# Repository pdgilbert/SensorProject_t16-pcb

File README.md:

# SensorProject_t16-pcb
Connect multiple temperature sensors to an analog digital converter.

##  Status: Prototype.

## Summary

Kicad project WIP.

PCB design to connect multiple (up to 16) thermistor temperature sensors to an ads1115 with I2C
output to connect to an MCU. Connectors are  2-pin JST XH_B2B-XH-A, as commonly used on NTC 10K 3950 sensors.
These sensors are inexpensive and easily available in lengths up to 3m. 
Measurements are broadcast with LoRa.

Related software is in repository https://github.com/pdgilbert/SensorProject_t16.

The `.png` and `jpg` files are produced from kicad in the `3D Viewer`  with `File > Export Current View as ...`.

## History

 - Version 0.2.2 2025-09 includes an stm32f411 MCU. It is not yet tested.

 - Version 0.2.0 2025-05 includes an stm32f411 MCU. It has a LoRa module RFM95W.
   It needs some hardware re-adjustment to work.

 - Version 0.1.1 2025-01 has pull up resistors added but has not been manufactured/tested.

 - Version 0.1.0 2024-05 needs manual addition of pull up resistors on the I2C lines. 
   With this modification it works with `blackpill` `stm32f401` or `stm32f411` inserted.
   This versin has no LoRa module.

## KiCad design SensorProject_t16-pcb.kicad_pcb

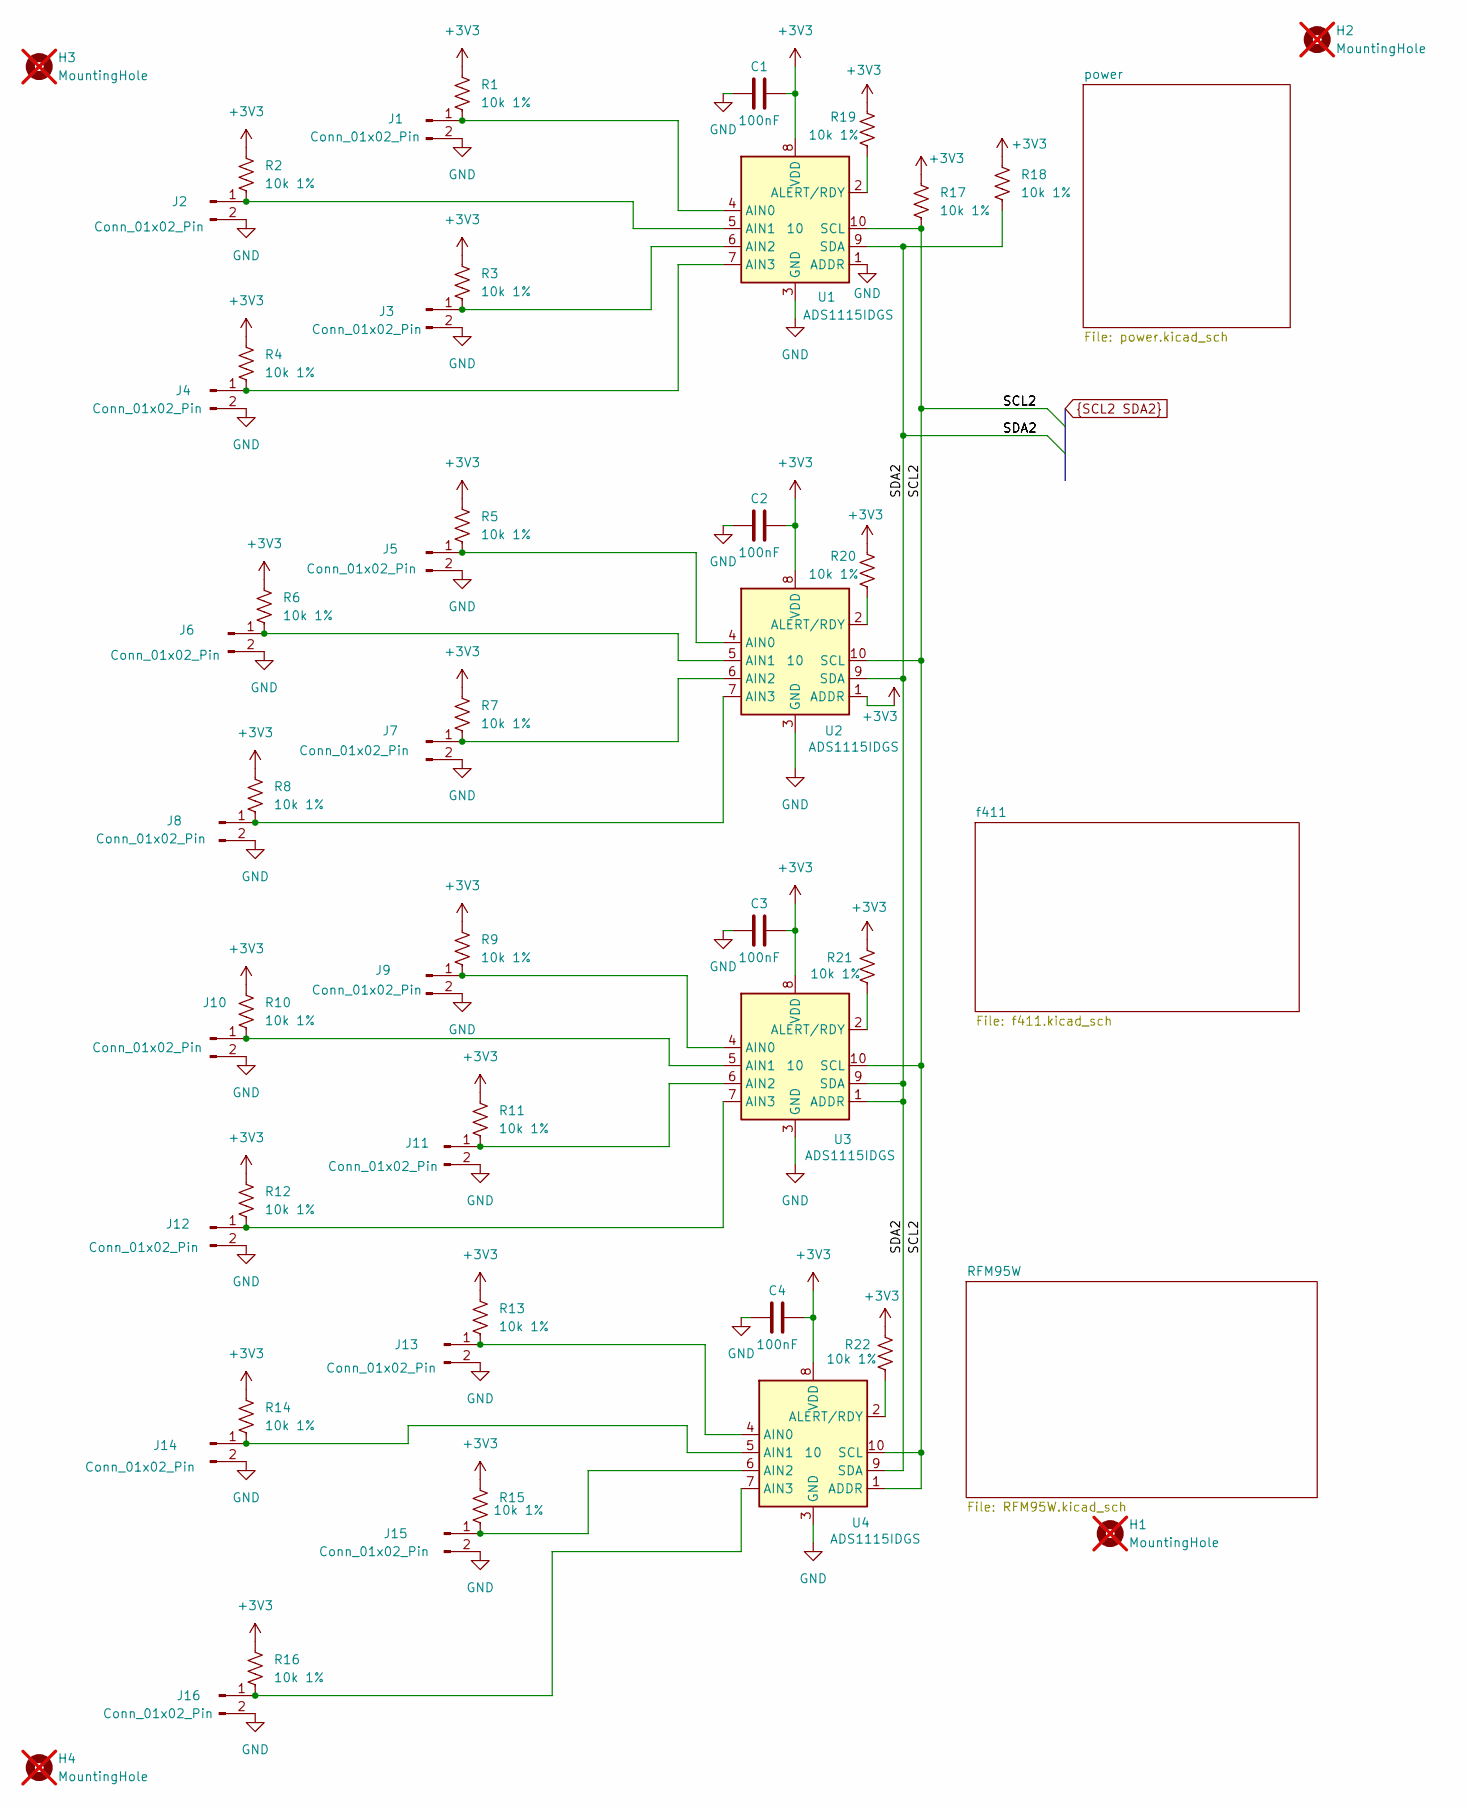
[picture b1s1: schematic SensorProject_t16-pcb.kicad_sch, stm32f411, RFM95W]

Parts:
C1, C2, C3, C4: 100nF; C_0402_1005Metric
H1, H2, H3, H4: MountingHole; MountingHole_2.2mm_M2_ISO7380_Pad; not fitted
J1, J2, J3, J4, J5, J6, J7, J8, J9, J10, J11, J12, J13, J14, J15, J16: Conn_01x02_Pin; JST_XH_B2B-XH-A_1x02_P2.50mm_Vertical; MfgPart B2B-XH-A
R1, R2, R3, R4, R5, R6, R7, R8, R9, R10, R11, R12, R13, R14, R15, R16, R17, R18, R19, R20, R21, R22: 10k 1%; R_0402_1005Metric
U1, U2, U3, U4: ADS1115IDGS; TSSOP-10_3x3mm_P0.5mm; MfgPart ADS1115IDGS

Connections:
+3V3: C1.1, C2.1, C3.1, C4.1, R1.1, R2.1, R3.1, R4.1, R5.1, R6.1, R7.1, R8.1, R9.1, R10.1, R11.1, R12.1, R13.1, R14.1, R15.1, R16.1, R17.1, R18.1, R19.1, R20.1, R21.1, R22.1, U1.8 (VDD), U2.1 (ADDR), U2.8 (VDD), U3.8 (VDD), U4.8 (VDD); also elsewhere on the board
GND: C1.2, C2.2, C3.2, C4.2, J1.2, J2.2, J3.2, J4.2, J5.2, J6.2, J7.2, J8.2, J9.2, J10.2, J11.2, J12.2, J13.2, J14.2, J15.2, J16.2, U1.1 (ADDR), U1.3 (GND), U2.3 (GND), U3.3 (GND), U4.3 (GND); also elsewhere on the board
unnamed: J1.1, R1.2, U1.4 (AIN0)
unnamed: J2.1, R2.2, U1.5 (AIN1)
unnamed: J3.1, R3.2, U1.6 (AIN2)
unnamed: J4.1, R4.2, U1.7 (AIN3)
unnamed: J5.1, R5.2, U2.4 (AIN0)
unnamed: J6.1, R6.2, U2.5 (AIN1)
unnamed: J7.1, R7.2, U2.6 (AIN2)
unnamed: J8.1, R8.2, U2.7 (AIN3)
unnamed: J9.1, R9.2, U3.4 (AIN0)
unnamed: J10.1, R10.2, U3.5 (AIN1)
unnamed: J11.1, R11.2, U3.6 (AIN2)
unnamed: J12.1, R12.2, U3.7 (AIN3)
unnamed: J13.1, R13.2, U4.4 (AIN0)
unnamed: J14.1, R14.2, U4.5 (AIN1)
unnamed: J15.1, R15.2, U4.6 (AIN2)
unnamed: J16.1, R16.2, U4.7 (AIN3)
unnamed: R19.2, U1.2 (ALERT/RDY)
unnamed: R20.2, U2.2 (ALERT/RDY)
unnamed: R21.2, U3.2 (ALERT/RDY)
unnamed: R22.2, U4.2 (ALERT/RDY)
SCL2: R17.2, U1.10 (SCL), U2.10 (SCL), U3.10 (SCL), U4.1 (ADDR), U4.10 (SCL); also elsewhere on the board
SDA2: R18.2, U1.9 (SDA), U2.9 (SDA), U3.1 (ADDR), U3.9 (SDA), U4.9 (SDA); also elsewhere on the board

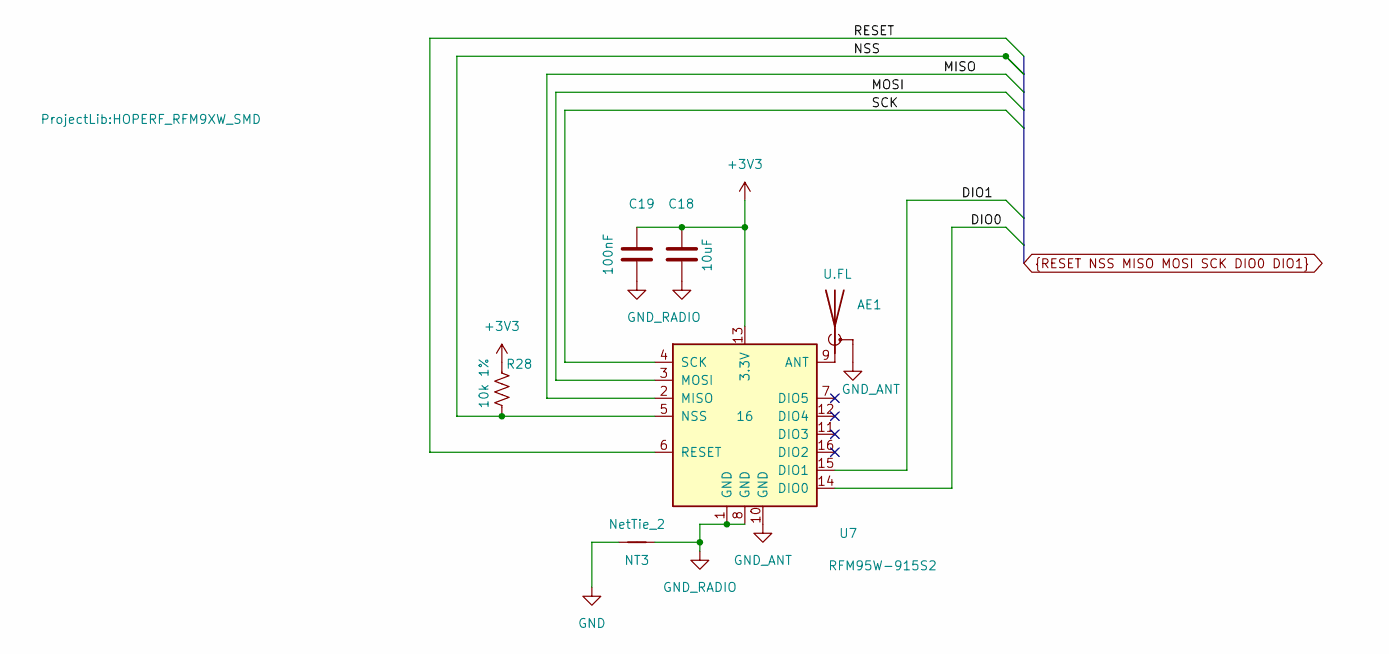
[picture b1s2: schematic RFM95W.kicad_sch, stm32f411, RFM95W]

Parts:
AE1: U.FL; U.FL_Molex_MCRF_73412-0110_Vertical; MfgPart U.FL-R-SMT-K(800)
C18: 10uF; C_0402_1005Metric
C19: 100nF; C_0402_1005Metric
NT3: NetTie_2; NetTie-2_SMD_Pad0.5mm
R28: 10k 1%; R_0402_1005Metric
U7: RFM95W-915S2; HOPERF_RFM9XW_SMD; MfgPart RFM95W-915S2

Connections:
+3V3: C18.1, C19.1, R28.1, U7.13 (3.3V); also elsewhere on the board
DIO0: U7.14 (DIO0); also elsewhere on the board
DIO1: U7.15 (DIO1); also elsewhere on the board
GND: NT3.1; also elsewhere on the board
GND_ANT: AE1.2 (Shield), U7.10 (GND)
GND_RADIO: C18.2, C19.2, NT3.2, U7.1 (GND), U7.8 (GND)
MISO: U7.2 (MISO); also elsewhere on the board
MOSI: U7.3 (MOSI); also elsewhere on the board
NSS: R28.2, U7.5 (NSS); also elsewhere on the board
unnamed: AE1.1 (A), U7.9 (ANT)
RESET: U7.6 (RESET); also elsewhere on the board
SCK: U7.4 (SCK); also elsewhere on the board

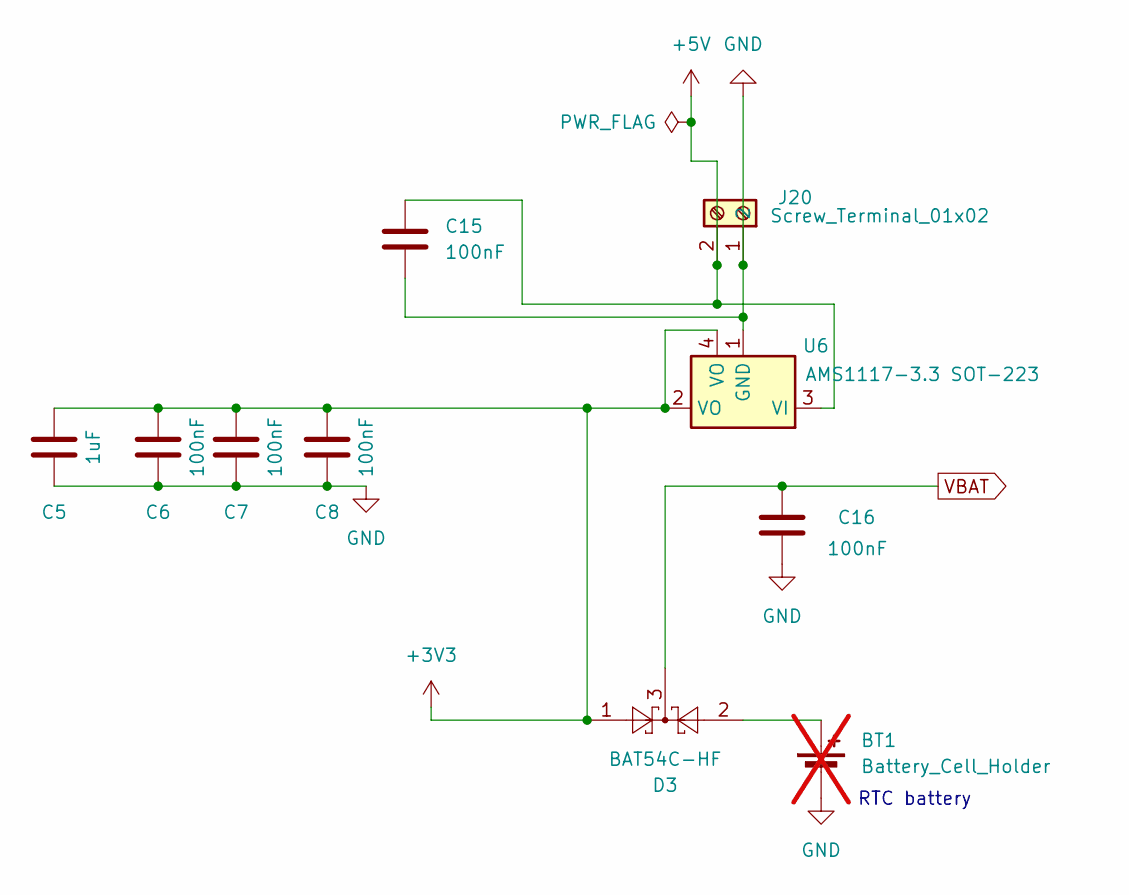
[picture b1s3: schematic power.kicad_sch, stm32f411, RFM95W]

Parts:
BT1: Battery_Cell_Holder; BatteryHolder_LINX_BAT-HLD-012-SMT; MfgPart BAT-HLD-012-SMT; not fitted
C5: 1uF; C_0402_1005Metric
C6, C7, C8, C15, C16: 100nF; C_0402_1005Metric
D3: BAT54C-HF; SOT-23; MfgPart BAT54C-HF
J20: Screw_Terminal_01x02; TerminalBlock_Phoenix_MPT-0,5-2-2.54_1x02_P2.54mm_Horizontal; MfgPart KF128-2.54-2P
U6: AMS1117-3.3 SOT-223; SOT-223; MfgPart AMS1117-3.3

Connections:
+3V3: C5.1, C6.1, C7.1, C8.1, D3.1, U6.2 (VO), U6.4 (VO); also elsewhere on the board
+5V: C15.1, J20.2, U6.3 (VI)
GND: BT1.2 (-), C5.2, C6.2, C7.2, C8.2, C15.2, C16.2, J20.1, U6.1 (GND); also elsewhere on the board
unnamed: BT1.1 (+), D3.2
VBAT: C16.1, D3.3; also elsewhere on the board

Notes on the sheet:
RTC battery

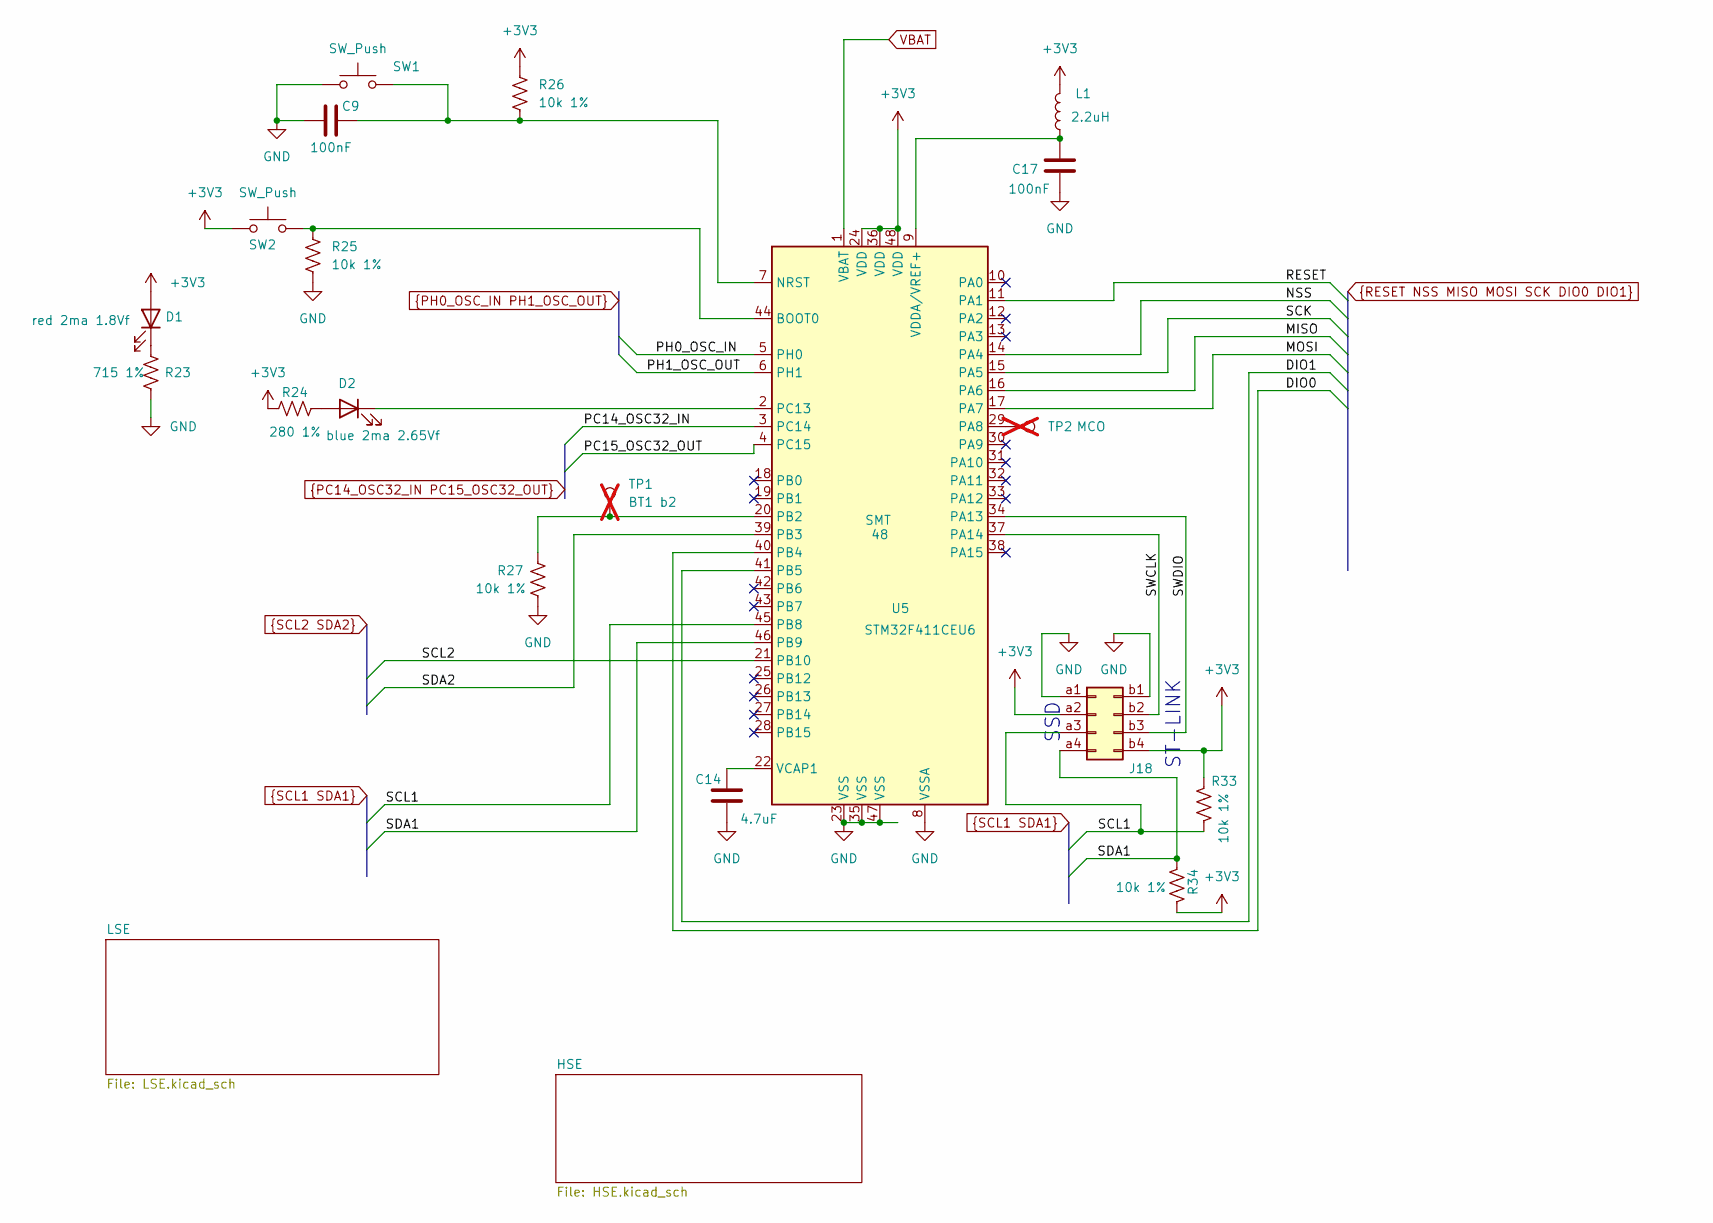
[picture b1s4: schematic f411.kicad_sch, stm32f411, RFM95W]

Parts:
C9, C17: 100nF; C_0402_1005Metric
C14: 4.7uF; C_0402_1005Metric
D1: red 2ma 1.8Vf; LED_0603_1608Metric; MfgPart APT1608LSECK/J3-PRV
D2: blue 2ma 2.65Vf; LED_0603_1608Metric; MfgPart APT1608LVBC/D
J18: Conn_02x04_Top_Bottom; PinSocket_2x04_P2.54mm_Vertical_SMD; MfgPart HC-PM254-5.0H-2x4PS-02A
L1: 2.2uH; L_0402_1005Metric; MfgPart MLZ1005M2R2WT000
R23: 715 1%; R_0402_1005Metric
R24: 280 1%; R_0402_1005Metric
R25, R26, R27, R33, R34: 10k 1%; R_0402_1005Metric
SW1, SW2: SW_Push; SW_SPST_B3U-1000P; MfgPart B3U-1000P
TP1: BT1 b2; TestPoint_Pad_D1.0mm; not fitted
TP2: MCO; TestPoint_Pad_D1.0mm; not fitted
U5: STM32F411CEU6; QFN-48-1EP_7x7mm_P0.5mm_EP5.6x5.6mm; MfgPart STM32F411CEU6

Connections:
+3V3: D1.2 (A), J18.a2, J18.b4, L1.2, R24.1, R26.1, R33.1, R34.2, SW2.1, U5.24 (VDD), U5.36 (VDD), U5.48 (VDD); also elsewhere on the board
/f411/SWCLK: J18.b2, U5.37 (PA14)
/f411/SWDIO: J18.b3, U5.34 (PA13)
DIO0: U5.40 (PB4); also elsewhere on the board
DIO1: U5.41 (PB5); also elsewhere on the board
GND: C9.1, C14.2, C17.2, J18.a1, J18.b1, R23.2, R25.2, R27.2, SW1.1, U5.8 (VSSA), U5.23 (VSS), U5.35 (VSS), U5.47 (VSS), U5.49 (VSS); also elsewhere on the board
MISO: U5.16 (PA6); also elsewhere on the board
MOSI: U5.17 (PA7); also elsewhere on the board
NSS: U5.14 (PA4); also elsewhere on the board
unnamed: D1.1 (K), R23.1
unnamed: D2.2 (A), R24.2
unnamed: D2.1 (K), U5.2 (PC13)
unnamed: R25.1, SW2.2, U5.44 (BOOT0)
unnamed: C9.2, R26.2, SW1.2, U5.7 (NRST)
unnamed: TP2.1 (1_1), U5.29 (PA8)
unnamed: R27.1, TP1.1 (1_1), U5.20 (PB2)
unnamed: C14.1, U5.22 (VCAP1)
unnamed: C17.1, L1.1, U5.9 (VDDA/VREF+)
PC14_OSC32_IN: U5.3 (PC14); also elsewhere on the board
PC15_OSC32_OUT: U5.4 (PC15); also elsewhere on the board
PH0_OSC_IN: U5.5 (PH0); also elsewhere on the board
PH1_OSC_OUT: U5.6 (PH1); also elsewhere on the board
RESET: U5.11 (PA1); also elsewhere on the board
SCK: U5.15 (PA5); also elsewhere on the board
SCL1: J18.a3, R33.2, U5.45 (PB8)
SCL2: U5.21 (PB10); also elsewhere on the board
SDA1: J18.a4, R34.1, U5.46 (PB9)
SDA2: U5.39 (PB3); also elsewhere on the board
VBAT: U5.1 (VBAT); also elsewhere on the board

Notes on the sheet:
SSD
ST-LINK

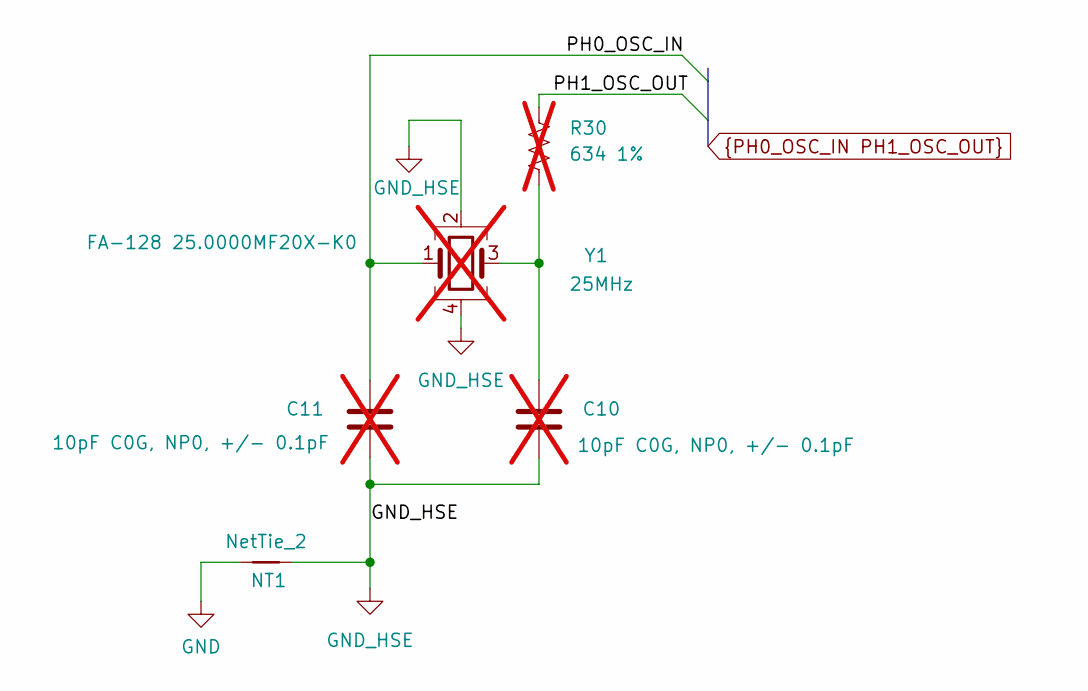
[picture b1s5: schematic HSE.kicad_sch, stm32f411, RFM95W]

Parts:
C10, C11: 10pF C0G, NP0, +/- 0.1pF; C_0402_1005Metric; not fitted
NT1: NetTie_2; NetTie-2_SMD_Pad0.5mm
R30: 634 1%; R_0402_1005Metric; not fitted
Y1: 25MHz; Crystal_SMD_2016-4Pin_2.0x1.6mm; MfgPart FA-128 25.0000MF20X-K0; not fitted

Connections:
GND: NT1.1; also elsewhere on the board
GND_HSE: C10.1, C11.1, NT1.2, Y1.2, Y1.4
unnamed: C10.2, R30.2, Y1.3
PH0_OSC_IN: C11.2, Y1.1; also elsewhere on the board
PH1_OSC_OUT: R30.1; also elsewhere on the board

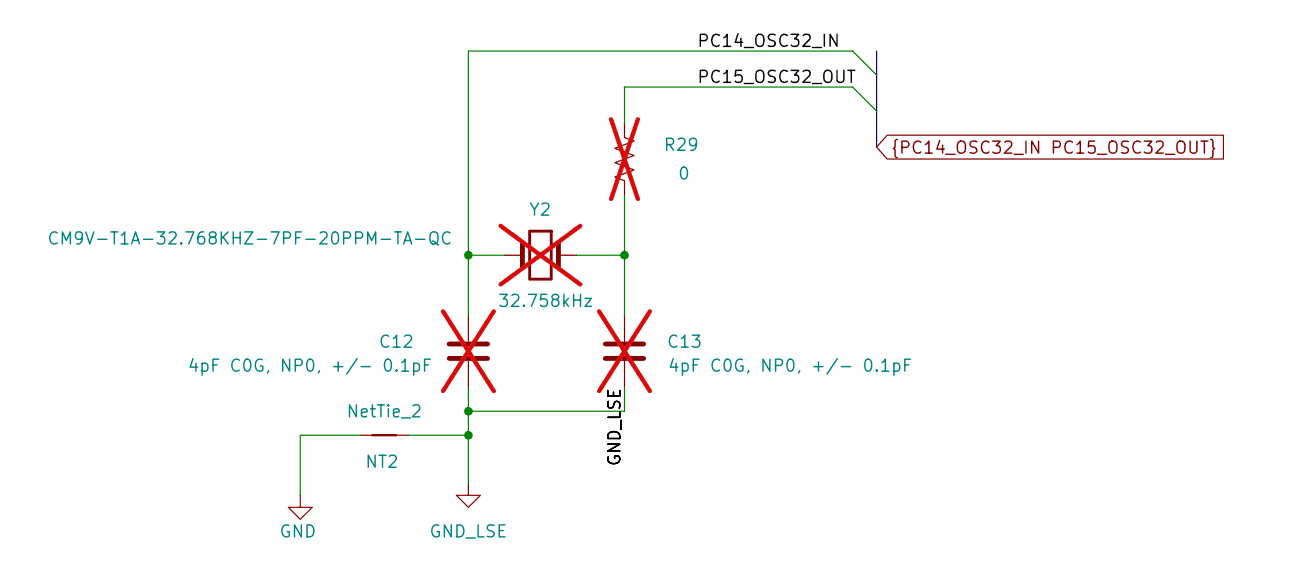
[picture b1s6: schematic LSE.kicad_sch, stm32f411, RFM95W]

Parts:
C12, C13: 4pF C0G, NP0, +/- 0.1pF; C_0402_1005Metric; not fitted
NT2: NetTie_2; NetTie-2_SMD_Pad0.5mm
R29: 0; R_0402_1005Metric; not fitted
Y2: 32.758kHz; Crystal_SMD_MicroCrystal_CM9V-T1A-2Pin_1.6x1.0mm; MfgPart CM9V-T1A-32.768KHZ-7PF-20PPM-TA-QC; not fitted

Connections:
GND: NT2.1; also elsewhere on the board
GND_LSE: C12.1, C13.1, NT2.2
unnamed: C13.2, R29.2, Y2.1
PC14_OSC32_IN: C12.2, Y2.2; also elsewhere on the board
PC15_OSC32_OUT: R29.1; also elsewhere on the board

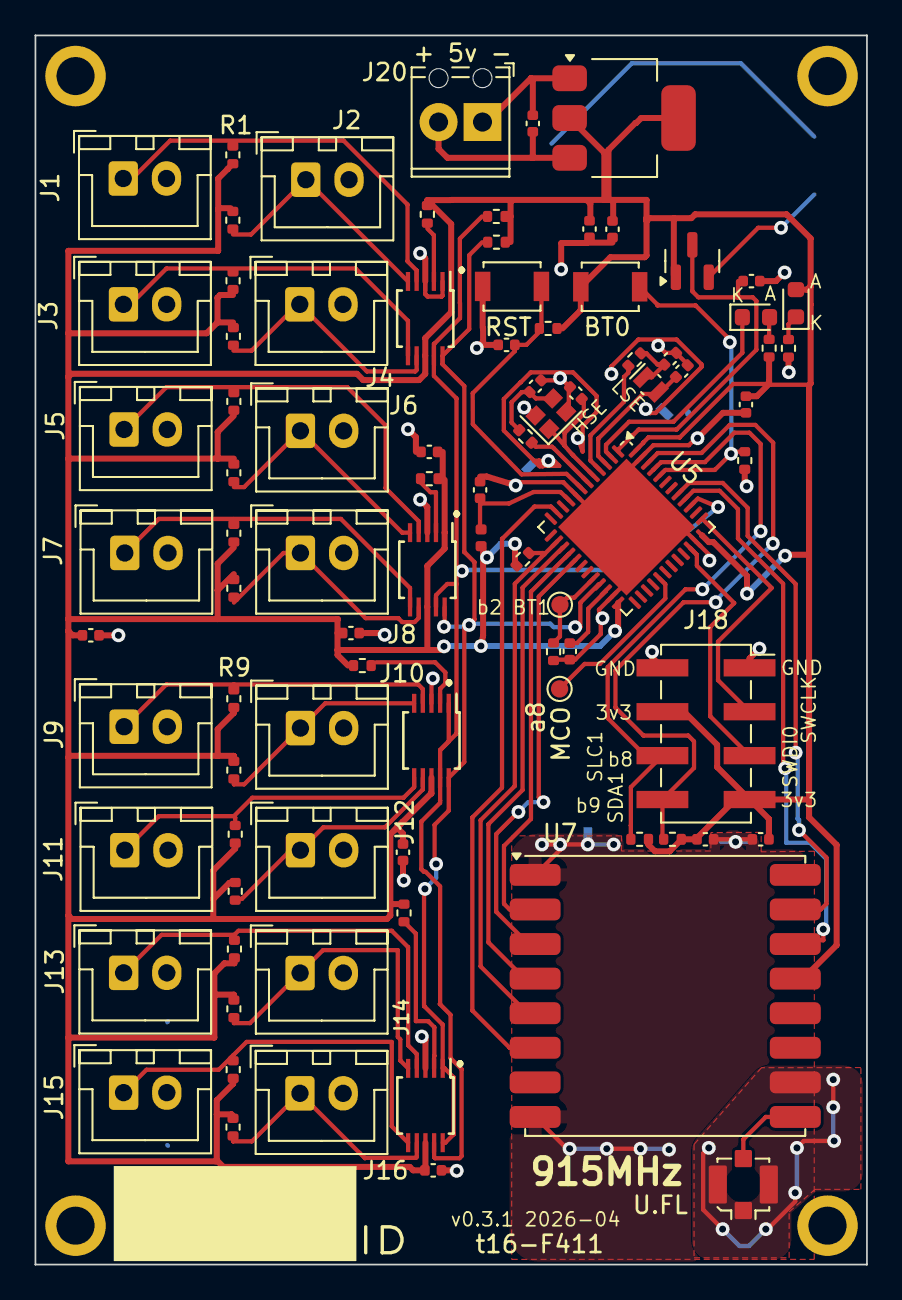
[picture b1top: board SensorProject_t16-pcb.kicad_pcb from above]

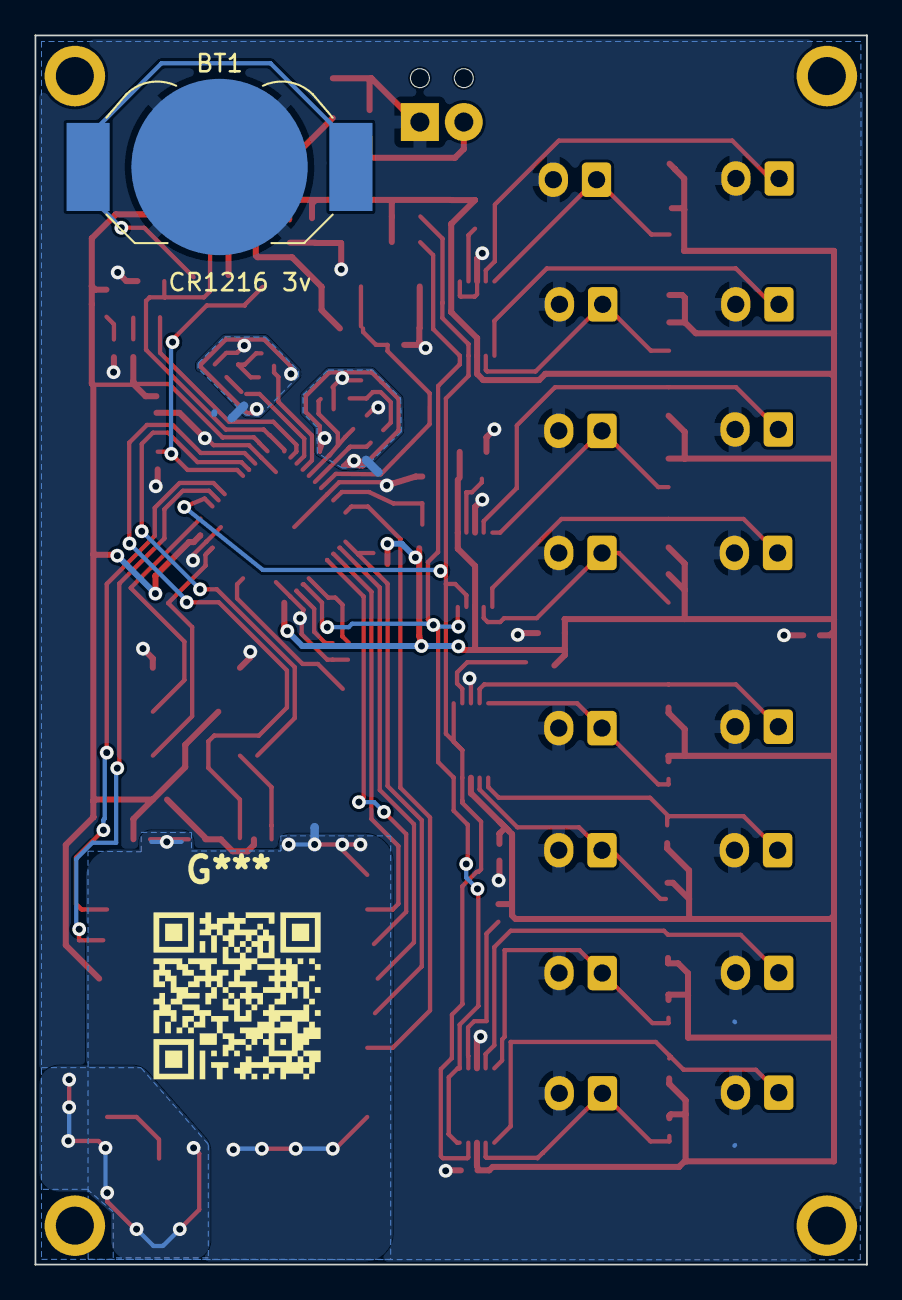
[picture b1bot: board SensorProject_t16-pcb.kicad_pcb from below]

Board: 2 copper layers, 48.1 x 71.1 mm, 95 parts (4 on the bottom side), 58 nets.

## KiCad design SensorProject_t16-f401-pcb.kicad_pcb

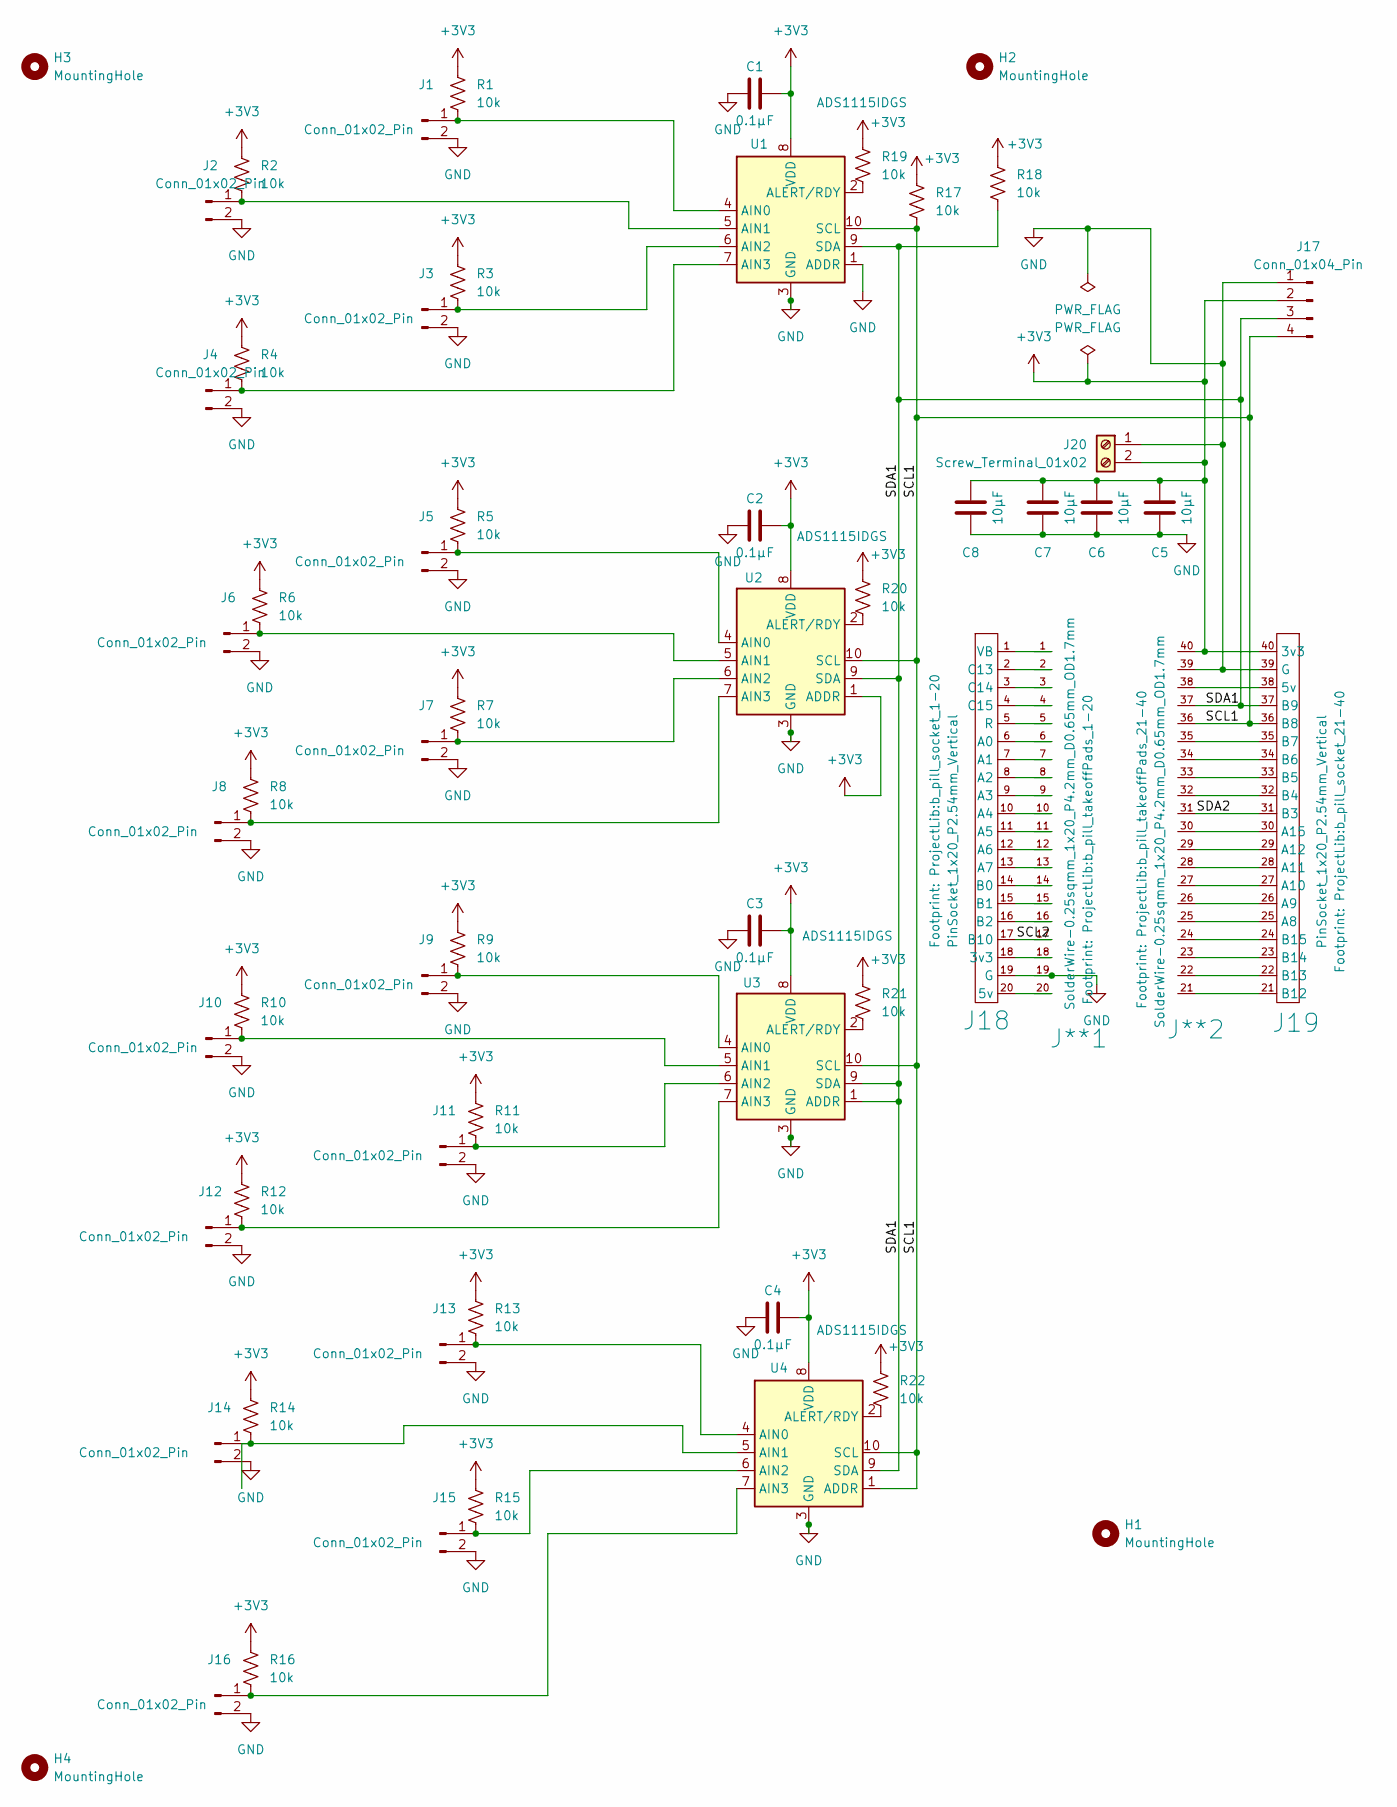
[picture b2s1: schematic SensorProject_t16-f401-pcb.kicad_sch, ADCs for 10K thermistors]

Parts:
C1, C2, C3, C4: 0.1µF; C_0805_2012Metric
C5, C6, C7, C8: 10µF; C_0805_2012Metric
H1, H2, H3, H4: MountingHole; MountingHole_2.2mm_M2_ISO7380_Pad
J1, J2, J3, J4, J5, J6, J7, J8, J9, J10, J11, J12, J13, J14, J15, J16: Conn_01x02_Pin; JST_XH_B2B-XH-A_1x02_P2.50mm_Vertical
J17: Conn_01x04_Pin; JST_XH_B4B-XH-A_1x04_P2.50mm_Vertical
J18: PinSocket_1x20_P2.54mm_Vertical; b_pill_socket_1-20
J19: PinSocket_1x20_P2.54mm_Vertical; b_pill_socket_21-40
J20: Screw_Terminal_01x02; TerminalBlock_Phoenix_MPT-0,5-2-2.54_1x02_P2.54mm_Horizontal
J**1: SolderWire-0.25sqmm_1x20_P4.2mm_D0.65mm_OD1.7mm; b_pill_takeoffPads_1-20
J**2: SolderWire-0.25sqmm_1x20_P4.2mm_D0.65mm_OD1.7mm; b_pill_takeoffPads_21-40
R1, R2, R3, R4, R5, R6, R7, R8, R9, R10, R11, R12, R13, R14, R15, R16, R17, R18, R19, R20, R21, R22: 10k; R_0603_1608Metric
U1, U2, U3, U4: ADS1115IDGS; TSSOP-10_3x3mm_P0.5mm

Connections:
+3V3: C1.1, C2.1, C3.1, C4.1, C5.1, C6.1, C7.1, C8.1, J17.2, J19.40 (3v3), J20.2, J**2.40, R1.1, R2.1, R3.1, R4.1, R5.1, R6.1, R7.1, R8.1, R9.1, R10.1, R11.1, R12.1, R13.1, R14.1, R15.1, R16.1, R17.1, R18.1, R19.1, R20.1, R21.1, R22.1, U1.8 (VDD), U2.1 (ADDR), U2.8 (VDD), U3.8 (VDD), U4.8 (VDD)
/SCL1: J17.4, J19.36 (B8), J**2.36, R17.2, U1.10 (SCL), U2.10 (SCL), U3.10 (SCL), U4.1 (ADDR), U4.10 (SCL)
/SCL2: J18.17 (B10), J**1.17
/SDA1: J17.3, J19.37 (B9), J**2.37, R18.2, U1.9 (SDA), U2.9 (SDA), U3.1 (ADDR), U3.9 (SDA), U4.9 (SDA)
/SDA2: J19.31 (B3), J**2.31
GND: C1.2, C2.2, C3.2, C4.2, C5.2, C6.2, C7.2, C8.2, J1.2, J2.2, J3.2, J4.2, J5.2, J6.2, J7.2, J8.2, J9.2, J10.2, J11.2, J12.2, J13.2, J14.2, J15.2, J16.2, J17.1, J18.19 (G), J19.39 (G), J20.1, J**1.19, J**2.39, U1.1 (ADDR), U1.3 (GND), U2.3 (GND), U3.3 (GND), U4.3 (GND)
unnamed: J1.1, R1.2, U1.4 (AIN0)
unnamed: J2.1, R2.2, U1.5 (AIN1)
unnamed: J3.1, R3.2, U1.6 (AIN2)
unnamed: J4.1, R4.2, U1.7 (AIN3)
unnamed: J5.1, R5.2, U2.4 (AIN0)
unnamed: J6.1, R6.2, U2.5 (AIN1)
unnamed: J7.1, R7.2, U2.6 (AIN2)
unnamed: J8.1, R8.2, U2.7 (AIN3)
unnamed: J9.1, R9.2, U3.4 (AIN0)
unnamed: J10.1, R10.2, U3.5 (AIN1)
unnamed: J11.1, R11.2, U3.6 (AIN2)
unnamed: J12.1, R12.2, U3.7 (AIN3)
unnamed: J13.1, R13.2, U4.4 (AIN0)
unnamed: J14.1, R14.2, U4.5 (AIN1)
unnamed: J15.1, R15.2, U4.6 (AIN2)
unnamed: J16.1, R16.2, U4.7 (AIN3)
unnamed: J18.18 (3v3), J**1.18
unnamed: J18.20 (5v), J**1.20
unnamed: J18.6 (A0), J**1.6
unnamed: J18.7 (A1), J**1.7
unnamed: J18.8 (A2), J**1.8
unnamed: J18.9 (A3), J**1.9
unnamed: J18.10 (A4), J**1.10
unnamed: J18.11 (A5), J**1.11
unnamed: J18.12 (A6), J**1.12
unnamed: J18.13 (A7), J**1.13
unnamed: J18.14 (B0), J**1.14
unnamed: J18.15 (B1), J**1.15
unnamed: J18.16 (B2), J**1.16
unnamed: J18.2 (C13), J**1.2
unnamed: J18.3 (C14), J**1.3
unnamed: J18.4 (C15), J**1.4
unnamed: J18.5 (R), J**1.5
unnamed: J18.1 (VB), J**1.1
unnamed: J19.38 (5v), J**2.38
unnamed: J19.25 (A8), J**2.25
unnamed: J19.26 (A9), J**2.26
unnamed: J19.27 (A10), J**2.27
unnamed: J19.28 (A11), J**2.28
unnamed: J19.29 (A12), J**2.29
unnamed: J19.30 (A15), J**2.30
unnamed: J19.32 (B4), J**2.32
unnamed: J19.33 (B5), J**2.33
unnamed: J19.34 (B6), J**2.34
unnamed: J19.35 (B7), J**2.35
unnamed: J19.21 (B12), J**2.21
unnamed: J19.22 (B13), J**2.22
unnamed: J19.23 (B14), J**2.23
unnamed: J19.24 (B15), J**2.24
unnamed: R19.2, U1.2 (ALERT/RDY)
unnamed: R20.2, U2.2 (ALERT/RDY)
unnamed: R21.2, U3.2 (ALERT/RDY)
unnamed: R22.2, U4.2 (ALERT/RDY)

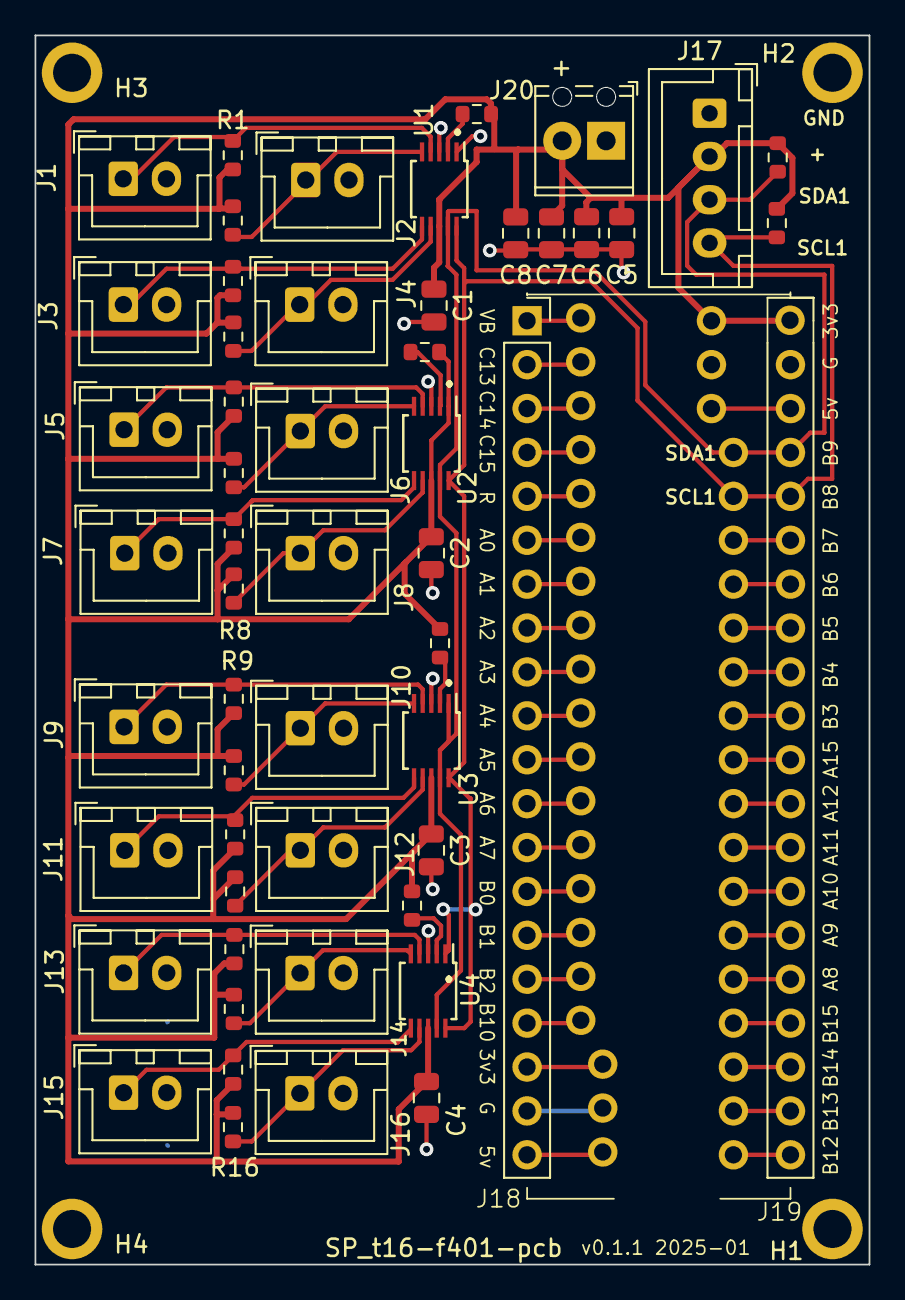
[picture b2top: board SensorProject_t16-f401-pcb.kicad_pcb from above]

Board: 2 copper layers, 48.3 x 71.1 mm, 60 parts (0 on the bottom side), 59 nets.

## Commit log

2023-08-08 switched license to GPL 3 (rather than CC) as kicad input seems more like code than copyrightable material. Perhaps will us CC for outputs.
2023-08-09 initial rough design, v0.0.1
2023-08-09 snapshot v0.0.10
2023-08-09 additinal files for v0.0.10
2023-08-10 more v0.0.10 files.
2023-08-10 changes for v0.0.12
2023-08-10 v0.0.14 snapshot.
2023-08-11 snapshot v0.1.0-pre
2023-08-15 change solder mask for takeoff pads, which will not be soldered.
2023-08-16 adjustments to mask and silkscreen.
2023-08-17 moved PG.kicad_sym to ProjectLib.kicad_sym and added all project symbols so project has a complete set of stable symbols.
2023-08-17 adding ProjectLib.pretty so all footprints are stable.
2023-08-26 footprint lib adjustments.
2023-08-29 ongoing cleanup.
2023-09-07 ongoing minor adjustments.
2023-09-07 moved connectors J17 and J20 and mounting hole H2 so power wire connection is in a better place.
2023-09-07 added 2 more noise caps on power line. Ongoing attempt to update PCB from schematic and keep footprint links to ProjectLib.
2023-09-14 added 2 more power noise caps and changed to 10muF.
2023-09-15 sized slightly larger, added 2 more mounting holes.
2024-04-18 Footprint adjustments to get tthem all from ProjectLib.pretty. Using Kicad 8.0.1.
2024-05-20 Removed test points because there is no room. Trying to sync symbol footprints and pcb footprints.
2024-05-20 DRC runs clean.
2024-06-02 as first submit to PCBway.
2024-08-15 added pullup on scl, sda. Other ongoing minor adjustments.
2024-08-15 fixed solde mask on takeoffPads.
2025-01-06 added pngs and notes.
2025-01-06 mv/rename ads1115with16JTS to SensorProject_t16-f401-pcb
2025-01-07 added 10k pullups on ads alert/rdy pins.
2025-01-07 png name adjustments from rename, for README.
2025-01-07 Adjusted rename for better convention.
2025-01-20 adding sheets for power, radio, and f401.
2025-02-01 ongoing add MCU and radio.
2025-02-08 ERC passing, Crytals not specified. Considering reverse polarity safeguard.
2025-02-21 f401.kicad_sch mostly complete other than xtals. Considering switch to f411 for memory, FPU, and generation 2 oscillator that gives better crystal choices.
2025-03-04 switched to F411. Added sheets for LSE and HSE.
2025-03-20 layout with F411 roughly good but needs work.
2025-03-25 Most routing done but not checked. Moat around HSE but no net-tie yet.
2025-03-25 some minor change when loaded by new kicad version.
2025-04-01 Moats complete. No errors. Net tie needs better zone and check crystals, BoM, etc. And general review.
2025-04-12 battery needs work.
2025-04-13 battery in place. Need HSE xtal spec.
2025-04-28 near complete, DRC good, ERC has a spurious error about ground on Y1.
2025-05-07 cleanup, ready to submit.
2025-08-22 As made, t16-F411 v0.2.0 2025-05, with added notes about needed fixes and results from some testing.
2025-08-27 Most post v0.2.0 fixes done. About to mess with GND_ANT zone and net.
2025-08-28 Added U.FL for antenna, with GND_ANT zone.
2025-08-31 BOM cleaned up.
2025-08-31 added test pad access to PB2 for boot1, renames J18 to TP2.
2025-09-01 flip side for radio in progress.
2025-09-01 most fixes for v0.2.0 done. Starting some improvements.
2025-09-01 finished flipping radio side.
2025-09-01 radio flip final cleanup.
2025-09-01 completed cleanup of v0.2.0 fixes and switch radio side.
2025-09-02 converted R, C, and L to smaller 0402 footprints. Some trace rearranging and cleanup.
2025-09-02 adding 0402_1005Metric footprints now in use.
2025-09-05 some (documentation) cleanup while submitting for fabrication.
2025-10-18 v0.2.2 with BOM fixes, some additional documentation and cleanup.
2025-11-29 improved schematic sheet titles.
2026-04-02 minor, pre kicad v10 upgrade.
2026-04-05 added new battery holder footprint.
2026-04-07 ongoing.
2026-04-10 added gnd-radio and gnd-ant zones on two layers. ERC and DRC mostly good. (Two warnings about pads field in NetTie footprints.)
2026-04-10 added caps to radio_gnd.
2026-04-11 added ID white space and QR code.
2026-04-11 3dmodels converted from .wrl to .step because .wrl seem to be missing in kicad 10.
2026-04-12 Cleaned up v0.3.0 2026-04. LSE and HSE populated.
2026-04-13 added QR and ID blocks on silkscreen. Marked HSE and LSE as DNP. Revised version number to 0.3.1.
